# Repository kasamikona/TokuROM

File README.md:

# TokuROM
**A unified ROM displacement cable system**

## Overview
TokuROM is a collection of adapter PCBs with a unified cable pinout for flexible ROM displacement setups.
It allows ROM chips to be relocated or replaced with an equivalent device at the other end of a cable.
A typical use case is to put an EPROM socket somewhere you can access it on an assembled device.  

The majority of TokuROM parts are entirely passive, serving only to move signals from one place to another.
The cabling has a unified pinout which carries 16 data bits with up to 23 address bits,
or 8 data bits with up to 24 address bits (A-1 shared with D15).
The cable pinout is based on the popular 16-bit mask ROMs / EPROMs with a /BYTE input,
but may be passively adapted to almost any kind of ROM pinout.
There is also a provision for a few additional control signals such as a remote reset signal.  

In TokuROM terminology, the "target" is any system with a position for a ROM chip,
and the "remote" is a ROM chip or equivalent that has been relocated.
The boards are named accordingly, with additional "converter" boards for special purposes.  

## Cabling
There are two kinds of cabling used in TokuROM, with a simple mapping from one to the other.  

The first uses one or two IDC cables: 40-pin + 10-pin, or 40-pin alone.
IDC allows cheap readily-availble cables and connectors to be used,
and the choice of a split setup allows connecting smaller ROMs with fewer address lines via a more compact cable setup.
The 40-pin section is directly compatible with **non-JEDEC** 40-pin chips, like the 27C400 EPROM and similar mask ROMs,
and can be used with IDC DIP displacement plugs.
The 10-pin section carries additional address lines, extra power, a reset line, and some currently reserved pins.  

The second kind of cabling is 50-pin 0.5mm **same-side** (aka forward or type A) FFC.
These are much more compact than IDC so only use a single cable, and are suitable for smaller target packages.
The pinout is the same as the 40+10 IDC arrangement combined, with the 10-pin section at the "top" to keep
address lines grouped together for 42-pin or 44-pin targets, and the 40-pin section is below that.
FFC connectors are not rated for many insertion cycles, so these should be used for semi-permanent connections.
If a cable will be inserted and removed often, consider using two cables and a replaceable FFC coupler in the middle.  

IDC cables are keyed and will always be the correct orientation.
FFC cables are also not keyed and heavily orientation-dependent.
TokuROM uses same-side cables and appropriately mirrored pinouts between target and remote.  

*TODO: pinout diagrams*

## Included Boards
The following list will grow over time as I make more boards and connection types for a variety of uses.
Boards marked with `*` may be **untested** currently, assemble at your own risk.
I will of course aim to test all the boards as the project evolves.
Generally `I` suffix for IDC and `F` suffix for FFC connections.
Boards with neither of those may have both, or be too small for IDC in which case FFC is implied.  

Target boards:
- `Target-DIP40MI`\*: DIP40 to IDC40, mask-ROM pinout **not JEDEC**. Equivalent to IDC-DIP transition plug but GND pins shorted.
- `Target-DIP42I`\*: DIP42 to IDC40+10. Defaults to 16Mbit pinout (like 27C160), jumper for 32Mbit (like 27C322). A20-A22 and reset are brought out to pin headers.
- `Target-DIP42IH`\*: DIP42 to IDC40+header. Minimal pin header with extra address lines for compactness. Same 16/32Mbit jumper as Target-DIP42I.
- `Target-DIP42F`\*: DIP42 to FFC50. Same 16/32Mbit jumper as Target-DIP42I.
- `Target-SOP44`: SOP44 to FFC50, SMD mask-ROM pinout. Castellated board edges for soldering directly. Has a pad for reset signal.

Remote boards:
- `Remote-ZIF42`\*: ZIF48 to IDC40+10 and FFC50, for 40P/42P EPROMs. Has 16/32Mbit jumper, manual reset button, and A20-A22 + reset on a pin header.
- `Remote-TSOP48`: 50P FFC to TSOP48 NOR flash, 29F/29LV series pinout. Useful for semi-permanent setups. Program with the below converter. Some pins repurposed.

Converter boards:
- `Convert-Flash-TL866`: Programmer for NOR flash remote boards. Use with Xgecu TL866x "minipro" programmer and SN001-1 adapter board.

## Currently Planned
These boards don't exist or aren't ready for use yet but are planned to be added at some point.
You may politely nag me or donate if you'd like any particular one to happen a little faster.  

Target planned:
- `Target-DIP40J(I/F)`: JEDEC pinout version of DIP40 target, like 27C4096. Haven't routed yet as I have no devices that use this.
- `Target-DIP28(I/F)`: DIP28 to IDC40 or FFC50 for 8-bit ROMs.
- `Target-DIP40MF`: FFC50 version of DIP40M target.
- `Target-SOP40`: smaller version of SOP44 target for narrower SOP40 footprint. SOP44 target can manage it for now but fiddly to solder.

Remote planned:
- A flash-based Romulator, separate project but will use TokuROM interface.

Converter planned:
- IDC40+10 to FFC50 in a compact form. Not sure how to manage FFC orientation differences.
- Inline voltage translation for NOR flash remotes with modern LV flash. Not urgent as they can survive running at 5V.
- Combiners for 2 to 4 DIP40 or DIP28 targets into a single TokuROM cable, for devices with split ROMs.

## Notes on Assembling
Some of the boards, especially those with FFC connectors, require some very fine SMD soldering.
The boards don't currently use full part numbers for the BOM but I recommend using a PCB assembly service if you can.
FFC connectors are bottom-contact type, Hirose FH12 or clones, they are a very common type.

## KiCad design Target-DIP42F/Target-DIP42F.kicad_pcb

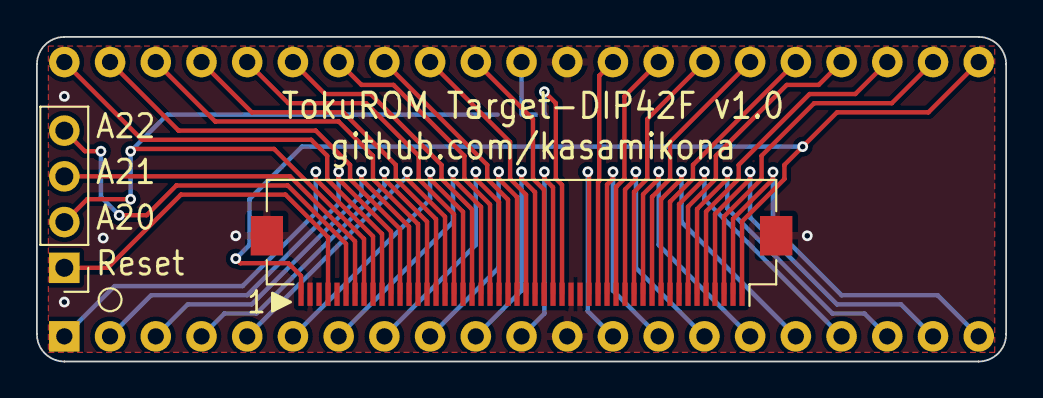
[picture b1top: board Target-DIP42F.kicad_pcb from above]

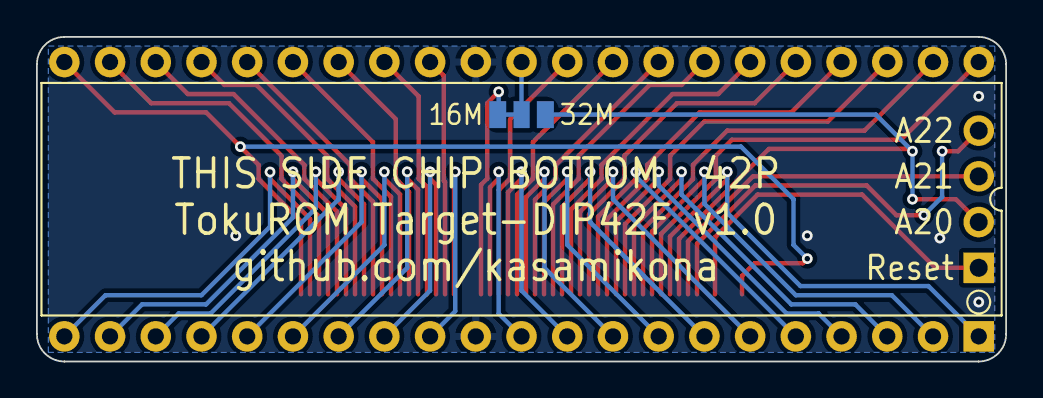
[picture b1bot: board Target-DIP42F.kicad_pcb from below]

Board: 2 copper layers, 53.8 x 18.0 mm, 4 parts (2 on the bottom side), 46 nets.

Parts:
J1: FFC-50
J2: DIP-42_Reversed_RoundCorner
J3: EXTRA; PinHeader_1x04_P2.54mm_Vertical
JP1: 16M/32M; SolderJumper-3_Custom

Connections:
/A0: J1.24, J2.10
/A1: J1.26, J2.9
/A2: J1.28, J2.8
/A3: J1.30, J2.7
/A4: J1.32, J2.6
/A5: J1.34, J2.5
/A6: J1.36, J2.4
/A7: J1.38, J2.3
/A8: J1.39, J2.41
/A9: J1.37, J2.40
/A10: J1.35, J2.39
/A11: J1.33, J2.38
/A12: J1.31, J2.37
/A13: J1.29, J2.36
/A14: J1.27, J2.35
/A15: J1.25, J2.34
/A16: J1.23, J2.33
/A17: J1.40, J2.2
/A18: J1.42, J2.1
/A19: J1.41, J2.42
/A20: J1.43, J3.2, JP1.3 (B)
/A21: J1.44, J3.3
/A22: J1.45, J3.4
/BYTE: J1.21, JP1.1 (A)
/BYTE_A20: J2.32, JP1.2 (C)
/CE: J1.22, J2.11
/D0: J1.16, J2.14
/D1: J1.12, J2.16
/D2: J1.8, J2.18
/D3: J1.4, J2.20
/D4: J1.3, J2.23
/D5: J1.7, J2.25
/D6: J1.11, J2.27
/D7: J1.15, J2.29
/D8: J1.14, J2.15
/D9: J1.10, J2.17
/D10: J1.6, J2.19
/D11: J1.2, J2.21
/D12: J1.5, J2.24
/D13: J1.9, J2.26
/D14: J1.13, J2.28
/D15: J1.17, J2.30
/GND: J1.19, J1.20, J1.49, J1.MP (MountPin), J2.12, J2.31
/OE: J1.18, J2.13
/TRESET: J1.47, J3.1
/VCC: J1.1, J1.50, J2.22

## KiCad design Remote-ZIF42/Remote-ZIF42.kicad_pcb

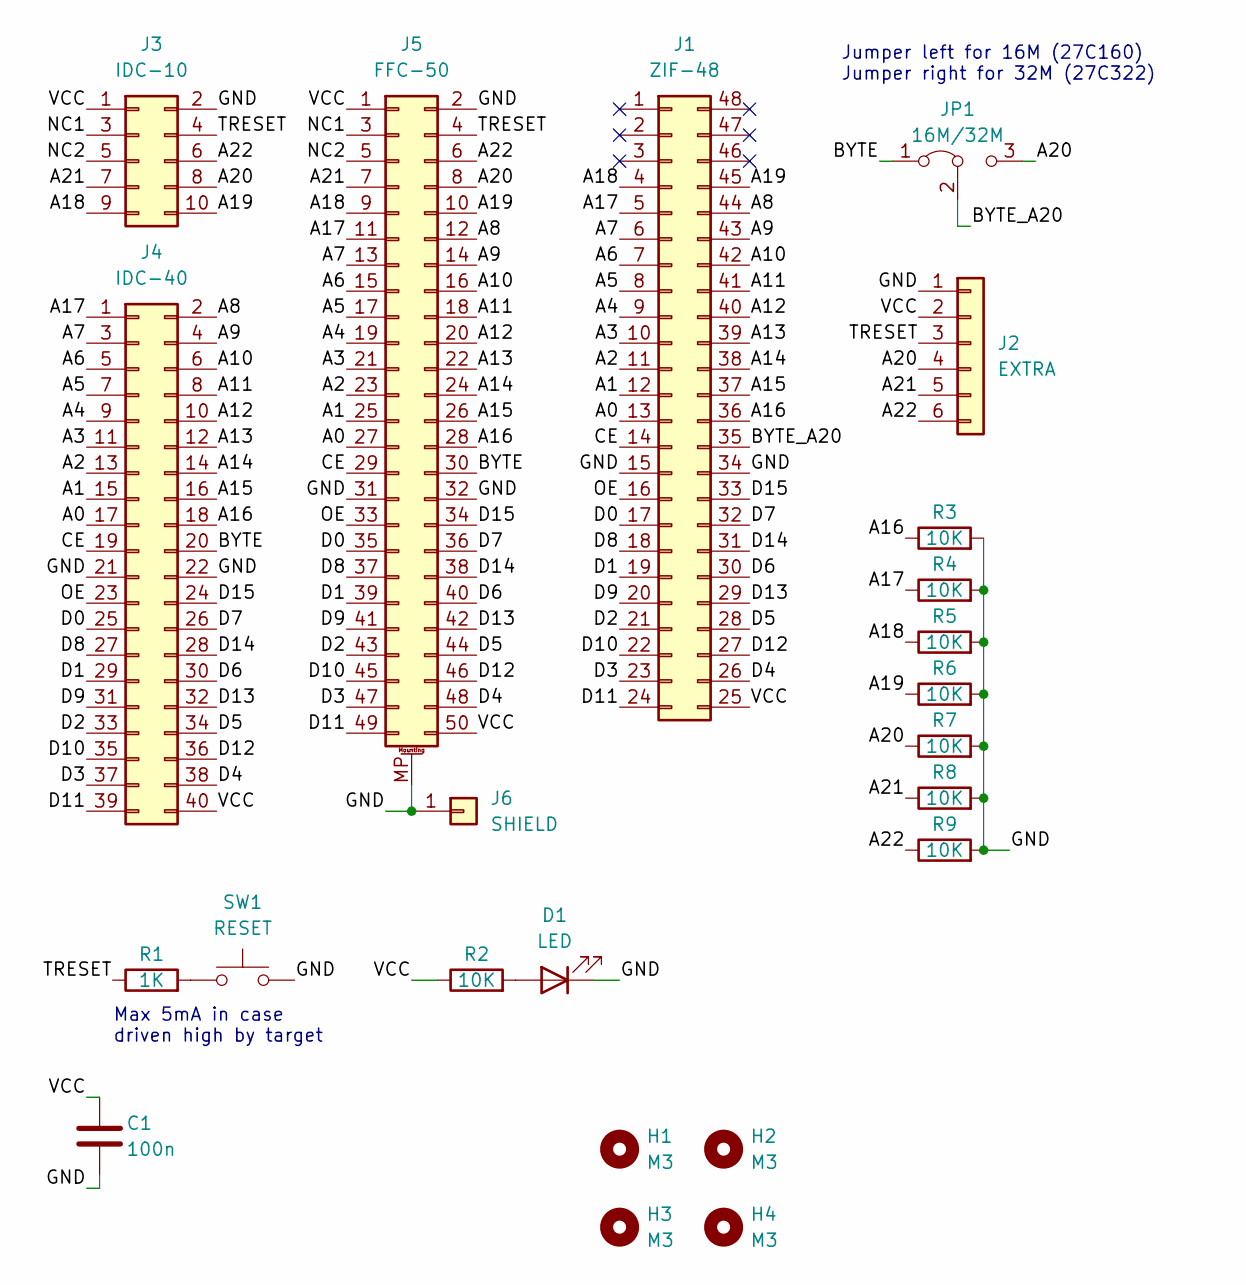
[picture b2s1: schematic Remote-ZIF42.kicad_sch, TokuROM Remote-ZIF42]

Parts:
C1: 100n; C_0805_2012Metric
D1: LED; LED_1206_3216Metric
H1, H2, H3, H4: M3; MountingHole_3.2mm_M3
J1: ZIF-48; ZIF-Socket-48P
J2: EXTRA; PinSocket_1x06_P2.54mm_Vertical
J3: IDC-10; IDC-Header_2x05_P2.54mm_Vertical
J4: IDC-40; IDC-Header_2x20_P2.54mm_Vertical
J5: FFC-50
J6: SHIELD; SolderPad-Large_Custom
JP1: 16M/32M; PinHeader_1x03_P2.54mm_Vertical
R1: 1K; R_0805_2012Metric
R2, R3, R4, R5, R6, R7, R8, R9: 10K; R_0805_2012Metric
SW1: RESET; SW_PUSH_6mm_H5mm

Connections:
/A0: J1.13, J4.17, J5.27
/A1: J1.12, J4.15, J5.25
/A2: J1.11, J4.13, J5.23
/A3: J1.10, J4.11, J5.21
/A4: J1.9, J4.9, J5.19
/A5: J1.8, J4.7, J5.17
/A6: J1.7, J4.5, J5.15
/A7: J1.6, J4.3, J5.13
/A8: J1.44, J4.2, J5.12
/A9: J1.43, J4.4, J5.14
/A10: J1.42, J4.6, J5.16
/A11: J1.41, J4.8, J5.18
/A12: J1.40, J4.10, J5.20
/A13: J1.39, J4.12, J5.22
/A14: J1.38, J4.14, J5.24
/A15: J1.37, J4.16, J5.26
/A16: J1.36, J4.18, J5.28, R3.1
/A17: J1.5, J4.1, J5.11, R4.1
/A18: J1.4, J3.9, J5.9, R5.1
/A19: J1.45, J3.10, J5.10, R6.1
/A20: J2.4, J3.8, J5.8, JP1.3 (B), R7.1
/A21: J2.5, J3.7, J5.7, R8.1
/A22: J2.6, J3.6, J5.6, R9.1
/BYTE: J4.20, J5.30, JP1.1 (A)
/BYTE_A20: J1.35, JP1.2 (C)
/CE: J1.14, J4.19, J5.29
/D0: J1.17, J4.25, J5.35
/D1: J1.19, J4.29, J5.39
/D2: J1.21, J4.33, J5.43
/D3: J1.23, J4.37, J5.47
/D4: J1.26, J4.38, J5.48
/D5: J1.28, J4.34, J5.44
/D6: J1.30, J4.30, J5.40
/D7: J1.32, J4.26, J5.36
/D8: J1.18, J4.27, J5.37
/D9: J1.20, J4.31, J5.41
/D10: J1.22, J4.35, J5.45
/D11: J1.24, J4.39, J5.49
/D12: J1.27, J4.36, J5.46
/D13: J1.29, J4.32, J5.42
/D14: J1.31, J4.28, J5.38
/D15: J1.33, J4.24, J5.34
/GND: C1.2, D1.1 (K), J1.15, J1.34, J2.1, J3.2, J4.21, J4.22, J5.2, J5.31, J5.32, J5.MP (MountPin), J6.1, R3.2, R4.2, R5.2, R6.2, R7.2, R8.2, R9.2, SW1.2
/NC1: J3.3, J5.3
/NC2: J3.5, J5.5
/OE: J1.16, J4.23, J5.33
/TRESET: J2.3, J3.4, J5.4, R1.1
/VCC: C1.1, J1.25, J2.2, J3.1, J4.40, J5.1, J5.50, R2.1
unnamed: D1.2 (A), R2.2
unnamed: R1.2, SW1.1

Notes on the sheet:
Max 5mA in case driven high by target
Jumper left for 16M (27C160) Jumper right for 32M (27C322)

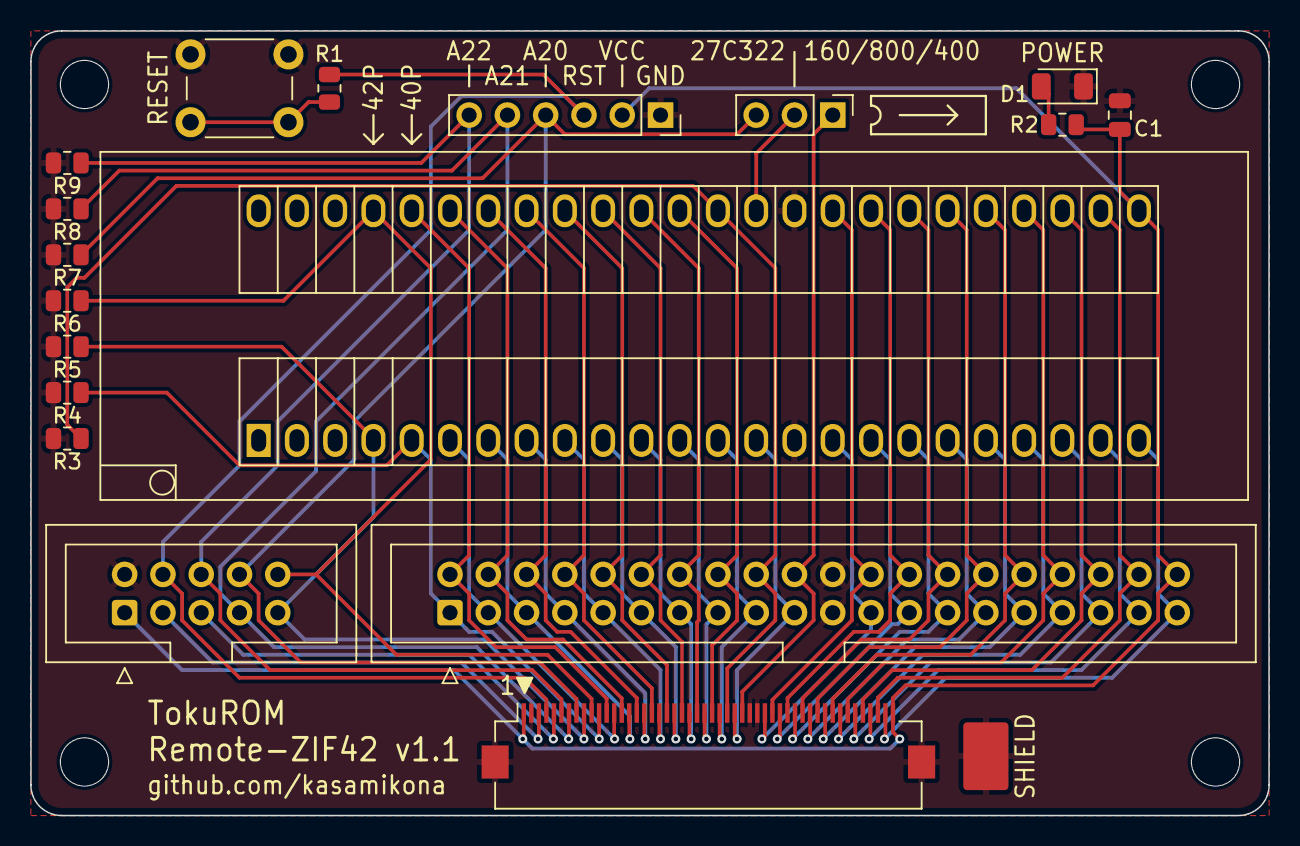
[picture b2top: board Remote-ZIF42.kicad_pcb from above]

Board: 2 copper layers, 82.2 x 52.1 mm, 23 parts (0 on the bottom side), 50 nets.

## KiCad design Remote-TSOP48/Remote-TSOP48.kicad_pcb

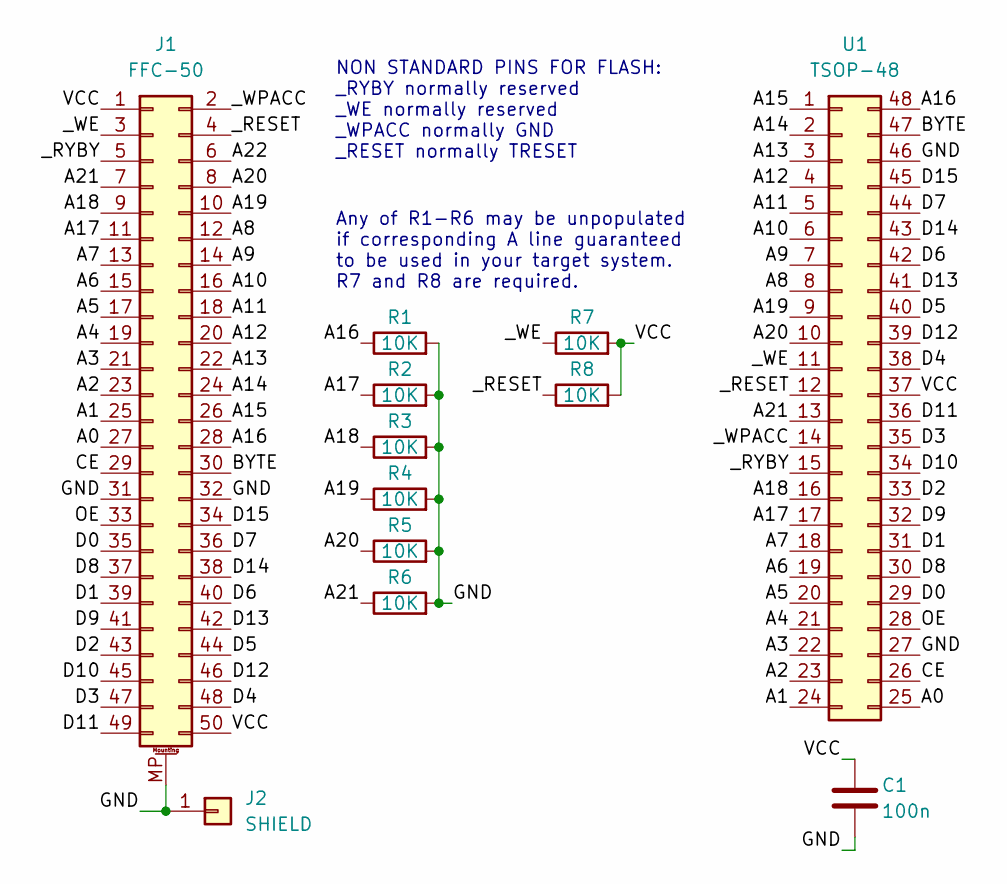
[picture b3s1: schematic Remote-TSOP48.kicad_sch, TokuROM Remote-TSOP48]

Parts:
C1: 100n; C_0603_1608Metric_Pad1.08x0.95mm_HandSolder
J1: FFC-50
J2: SHIELD; SolderPad-Small_Custom
R1, R2, R3, R4, R5, R6, R7, R8: 10K; R_0603_1608Metric_Pad0.98x0.95mm_HandSolder
U1: TSOP-48; TSOP-I-48_18.4x12mm_P0.5mm

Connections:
/A0: J1.27, U1.25
/A1: J1.25, U1.24
/A2: J1.23, U1.23
/A3: J1.21, U1.22
/A4: J1.19, U1.21
/A5: J1.17, U1.20
/A6: J1.15, U1.19
/A7: J1.13, U1.18
/A8: J1.12, U1.8
/A9: J1.14, U1.7
/A10: J1.16, U1.6
/A11: J1.18, U1.5
/A12: J1.20, U1.4
/A13: J1.22, U1.3
/A14: J1.24, U1.2
/A15: J1.26, U1.1
/A16: J1.28, R1.1, U1.48
/A17: J1.11, R2.1, U1.17
/A18: J1.9, R3.1, U1.16
/A19: J1.10, R4.1, U1.9
/A20: J1.8, R5.1, U1.10
/A21: J1.7, R6.1, U1.13
/A22: J1.6
/BYTE: J1.30, U1.47
/CE: J1.29, U1.26
/D0: J1.35, U1.29
/D1: J1.39, U1.31
/D2: J1.43, U1.33
/D3: J1.47, U1.35
/D4: J1.48, U1.38
/D5: J1.44, U1.40
/D6: J1.40, U1.42
/D7: J1.36, U1.44
/D8: J1.37, U1.30
/D9: J1.41, U1.32
/D10: J1.45, U1.34
/D11: J1.49, U1.36
/D12: J1.46, U1.39
/D13: J1.42, U1.41
/D14: J1.38, U1.43
/D15: J1.34, U1.45
/GND: C1.2, J1.31, J1.32, J1.MP (MountPin), J2.1, R1.2, R2.2, R3.2, R4.2, R5.2, R6.2, U1.27, U1.46; also elsewhere on the board
/OE: J1.33, U1.28
/VCC: C1.1, J1.1, J1.50, R7.2, R8.2, U1.37
/_RESET: J1.4, R8.1, U1.12
/_RYBY: J1.5, U1.15
/_WE: J1.3, R7.1, U1.11
/_WPACC: J1.2, U1.14

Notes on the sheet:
NON STANDARD PINS FOR FLASH: _RYBY normally reserved _WE normally reserved _WPACC normally GND _RESET normally TRESET
Any of R1-R6 may be unpopulated if corresponding A line guaranteed to be used in your target system. R7 and R8 are required.

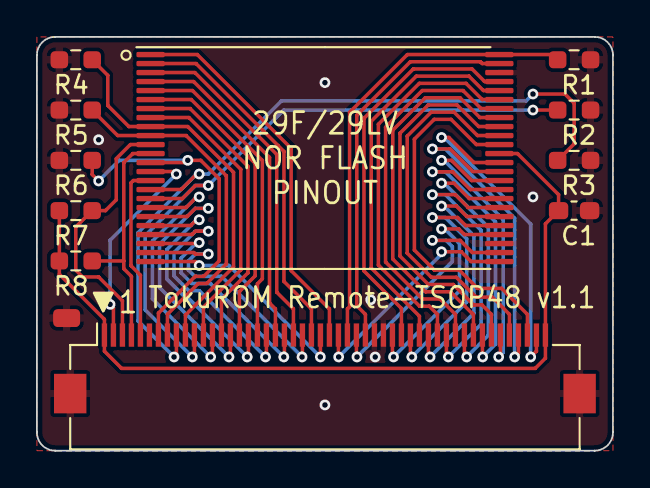
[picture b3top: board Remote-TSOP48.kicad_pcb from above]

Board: 2 copper layers, 32.0 x 23.0 mm, 12 parts (0 on the bottom side), 47 nets.

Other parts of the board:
J6: SHIELD; SolderPad-Small_Custom

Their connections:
/GND: J6.1; also elsewhere on the board

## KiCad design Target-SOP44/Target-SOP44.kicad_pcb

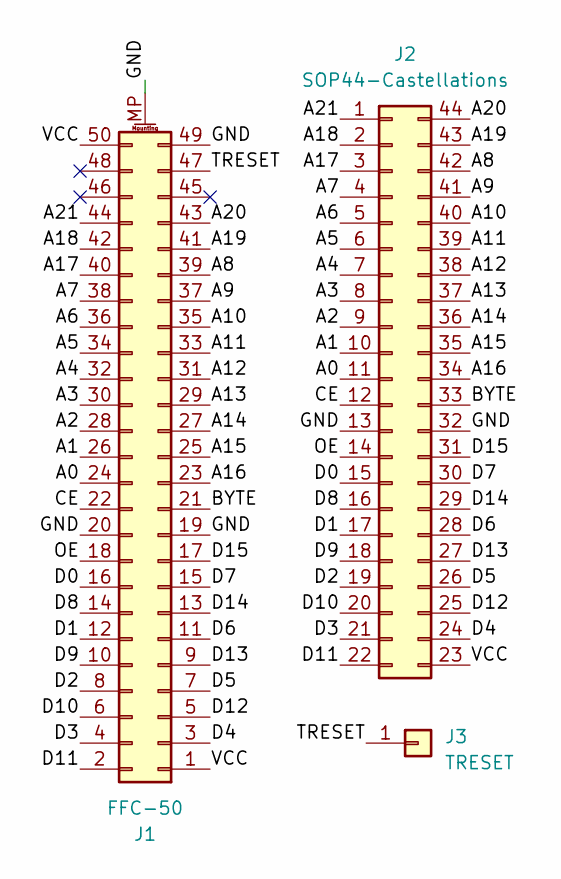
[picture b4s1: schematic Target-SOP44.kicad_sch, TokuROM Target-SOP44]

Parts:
J1: FFC-50; FFC-50_NarrowMount
J2: SOP44-Castellations
J3: TRESET; SolderPad-Small_Custom

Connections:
/A0: J1.24, J2.11
/A1: J1.26, J2.10
/A2: J1.28, J2.9
/A3: J1.30, J2.8
/A4: J1.32, J2.7
/A5: J1.34, J2.6
/A6: J1.36, J2.5
/A7: J1.38, J2.4
/A8: J1.39, J2.42
/A9: J1.37, J2.41
/A10: J1.35, J2.40
/A11: J1.33, J2.39
/A12: J1.31, J2.38
/A13: J1.29, J2.37
/A14: J1.27, J2.36
/A15: J1.25, J2.35
/A16: J1.23, J2.34
/A17: J1.40, J2.3
/A18: J1.42, J2.2
/A19: J1.41, J2.43
/A20: J1.43, J2.44
/A21: J1.44, J2.1
/BYTE: J1.21, J2.33
/CE: J1.22, J2.12
/D0: J1.16, J2.15
/D1: J1.12, J2.17
/D2: J1.8, J2.19
/D3: J1.4, J2.21
/D4: J1.3, J2.24
/D5: J1.7, J2.26
/D6: J1.11, J2.28
/D7: J1.15, J2.30
/D8: J1.14, J2.16
/D9: J1.10, J2.18
/D10: J1.6, J2.20
/D11: J1.2, J2.22
/D12: J1.5, J2.25
/D13: J1.9, J2.27
/D14: J1.13, J2.29
/D15: J1.17, J2.31
/GND: J1.19, J1.20, J1.49, J1.MP (MountPin), J2.13, J2.32
/OE: J1.18, J2.14
/TRESET: J1.47, J3.1
/VCC: J1.1, J1.50, J2.23

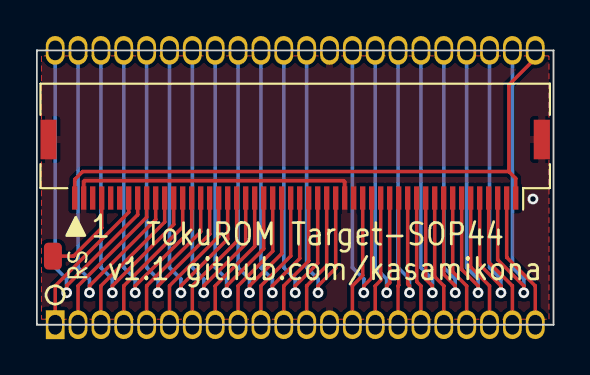
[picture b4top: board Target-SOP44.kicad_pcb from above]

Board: 2 copper layers, 28.7 x 15.2 mm, 3 parts (0 on the bottom side), 44 nets.

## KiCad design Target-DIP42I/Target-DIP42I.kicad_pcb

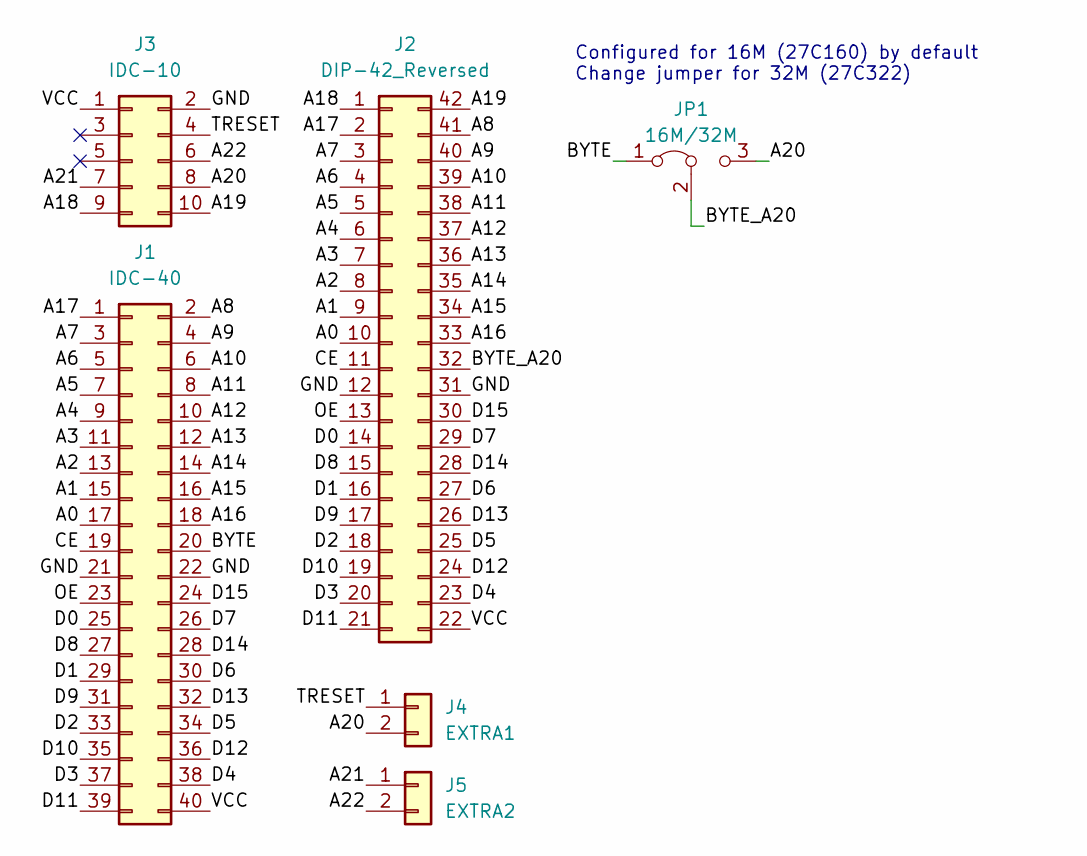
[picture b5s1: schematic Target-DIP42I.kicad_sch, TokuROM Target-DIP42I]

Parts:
J1: IDC-40; IDC-Header_2x20_P2.54mm_Vertical
J2: DIP-42_Reversed
J3: IDC-10; IDC-Header_2x05_P2.54mm_Vertical
J4: EXTRA1; PinHeader_1x02_P2.54mm_Vertical
J5: EXTRA2; PinHeader_1x02_P2.54mm_Vertical
JP1: 16M/32M; SolderJumper-3_Custom

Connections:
/A0: J1.17, J2.10
/A1: J1.15, J2.9
/A2: J1.13, J2.8
/A3: J1.11, J2.7
/A4: J1.9, J2.6
/A5: J1.7, J2.5
/A6: J1.5, J2.4
/A7: J1.3, J2.3
/A8: J1.2, J2.41
/A9: J1.4, J2.40
/A10: J1.6, J2.39
/A11: J1.8, J2.38
/A12: J1.10, J2.37
/A13: J1.12, J2.36
/A14: J1.14, J2.35
/A15: J1.16, J2.34
/A16: J1.18, J2.33
/A17: J1.1, J2.2
/A18: J2.1, J3.9
/A19: J2.42, J3.10
/A20: J3.8, J4.2, JP1.3 (B)
/A21: J3.7, J5.1
/A22: J3.6, J5.2
/BYTE: J1.20, JP1.1 (A)
/BYTE_A20: J2.32, JP1.2 (C)
/CE: J1.19, J2.11
/D0: J1.25, J2.14
/D1: J1.29, J2.16
/D2: J1.33, J2.18
/D3: J1.37, J2.20
/D4: J1.38, J2.23
/D5: J1.34, J2.25
/D6: J1.30, J2.27
/D7: J1.26, J2.29
/D8: J1.27, J2.15
/D9: J1.31, J2.17
/D10: J1.35, J2.19
/D11: J1.39, J2.21
/D12: J1.36, J2.24
/D13: J1.32, J2.26
/D14: J1.28, J2.28
/D15: J1.24, J2.30
/GND: J1.21, J1.22, J2.12, J2.31, J3.2
/OE: J1.23, J2.13
/TRESET: J3.4, J4.1
/VCC: J1.40, J2.22, J3.1

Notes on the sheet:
Configured for 16M (27C160) by default Change jumper for 32M (27C322)

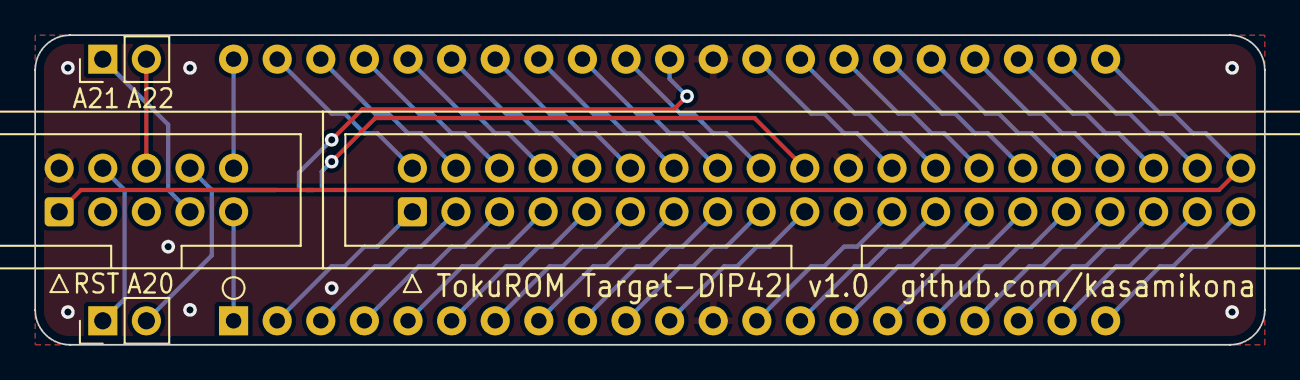
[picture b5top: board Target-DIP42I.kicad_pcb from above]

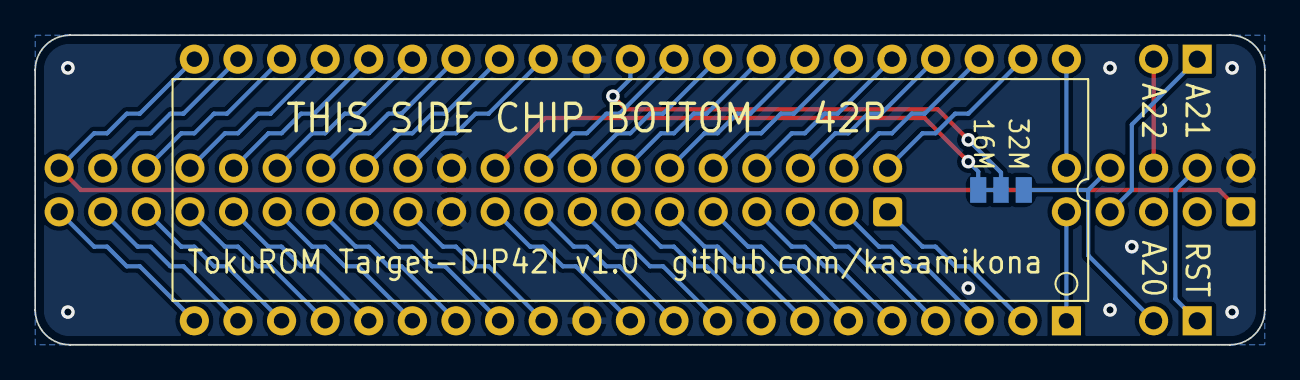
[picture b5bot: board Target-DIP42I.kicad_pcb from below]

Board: 2 copper layers, 71.6 x 18.0 mm, 6 parts (2 on the bottom side), 46 nets.

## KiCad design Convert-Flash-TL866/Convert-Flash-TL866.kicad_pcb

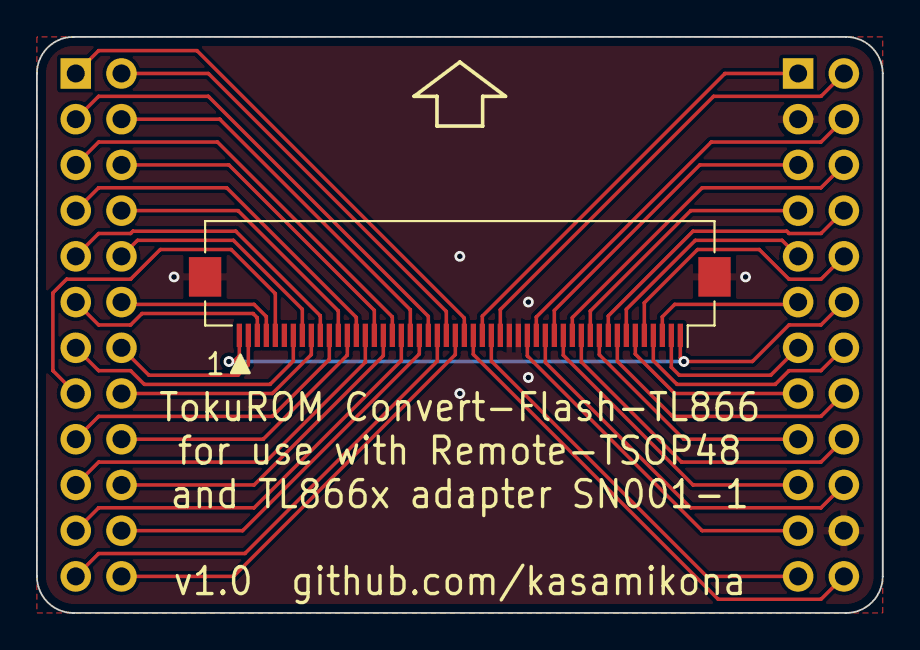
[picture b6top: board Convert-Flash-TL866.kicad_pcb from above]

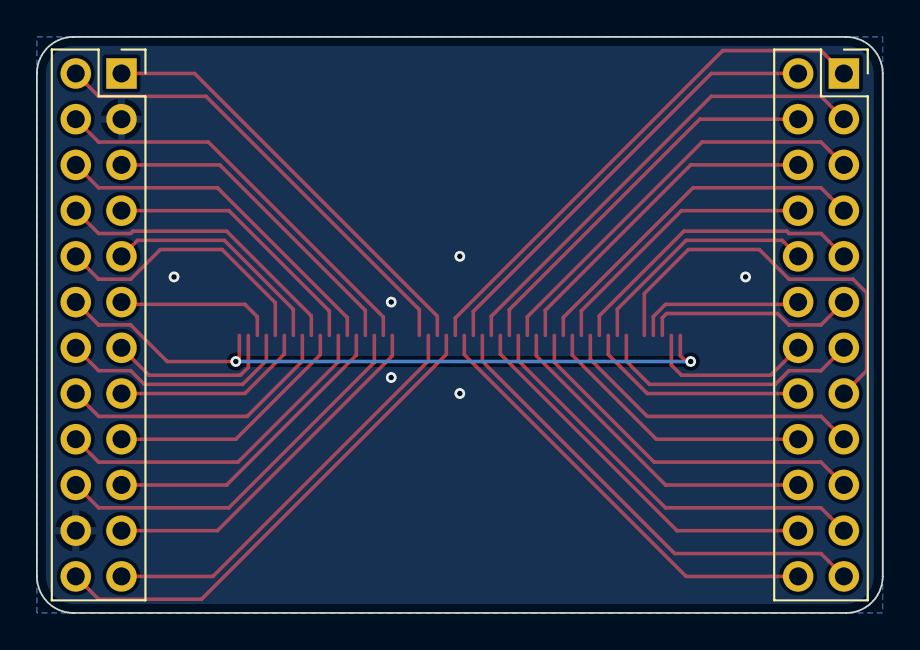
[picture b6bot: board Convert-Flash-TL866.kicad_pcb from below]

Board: 2 copper layers, 47.0 x 32.0 mm, 3 parts (2 on the bottom side), 47 nets.

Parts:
J1: FFC-50
J2: XG-TSOP-L; PinSocket_2x12_P2.54mm_Vertical
J3: XG-TSOP-R; PinSocket_2x12_P2.54mm_Vertical

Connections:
/A0: J1.24, J3.24
/A1: J1.26, J2.24
/A2: J1.28, J2.23
/A3: J1.30, J2.22
/A4: J1.32, J2.21
/A5: J1.34, J2.20
/A6: J1.36, J2.19
/A7: J1.38, J2.18
/A8: J1.39, J2.8
/A9: J1.37, J2.7
/A10: J1.35, J2.6
/A11: J1.33, J2.5
/A12: J1.31, J2.4
/A13: J1.29, J2.3
/A14: J1.27, J2.2
/A15: J1.25, J2.1
/A16: J1.23, J3.1
/A17: J1.40, J2.17
/A18: J1.42, J2.16
/A19: J1.41, J2.9
/A20: J1.43, J2.10
/A21: J1.44, J2.13
/BYTE: J1.21, J3.2
/CE: J1.22, J3.23
/D0: J1.16, J3.20
/D1: J1.12, J3.18
/D2: J1.8, J3.16
/D3: J1.4, J3.14
/D4: J1.3, J3.11
/D5: J1.7, J3.9
/D6: J1.11, J3.7
/D7: J1.15, J3.5
/D8: J1.14, J3.19
/D9: J1.10, J3.17
/D10: J1.6, J3.15
/D11: J1.2, J3.13
/D12: J1.5, J3.10
/D13: J1.9, J3.8
/D14: J1.13, J3.6
/D15: J1.17, J3.4
/GND: J1.19, J1.20, J1.MP (MountPin), J3.3, J3.22
/OE: J1.18, J3.21
/VCC: J1.1, J1.50, J3.12
/_RESET: J1.47, J2.12
/_RYBY: J1.46, J2.15
/_WE: J1.48, J2.11
/_WPACC: J1.49, J2.14

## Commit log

2024-07-13 Add rev1.0 designs, not all tested
2024-07-14 Slight renaming, add initial README
2024-08-17 Slightly enlarge Target-SOP44 outline for corner quality
2024-08-18 Promote enlarged Target-SOP44 to v1.1
2024-08-18 Remote-TSOP48 v1.1 accomodates 0603 or 0805 passives, connector moved down
2024-08-18 Fix minor routing issues
2024-08-21 Remote-ZIF42 v1.1 enlarge through-holes for socket, cleanup routing
2024-11-19 Add DIP42F target, update readme
